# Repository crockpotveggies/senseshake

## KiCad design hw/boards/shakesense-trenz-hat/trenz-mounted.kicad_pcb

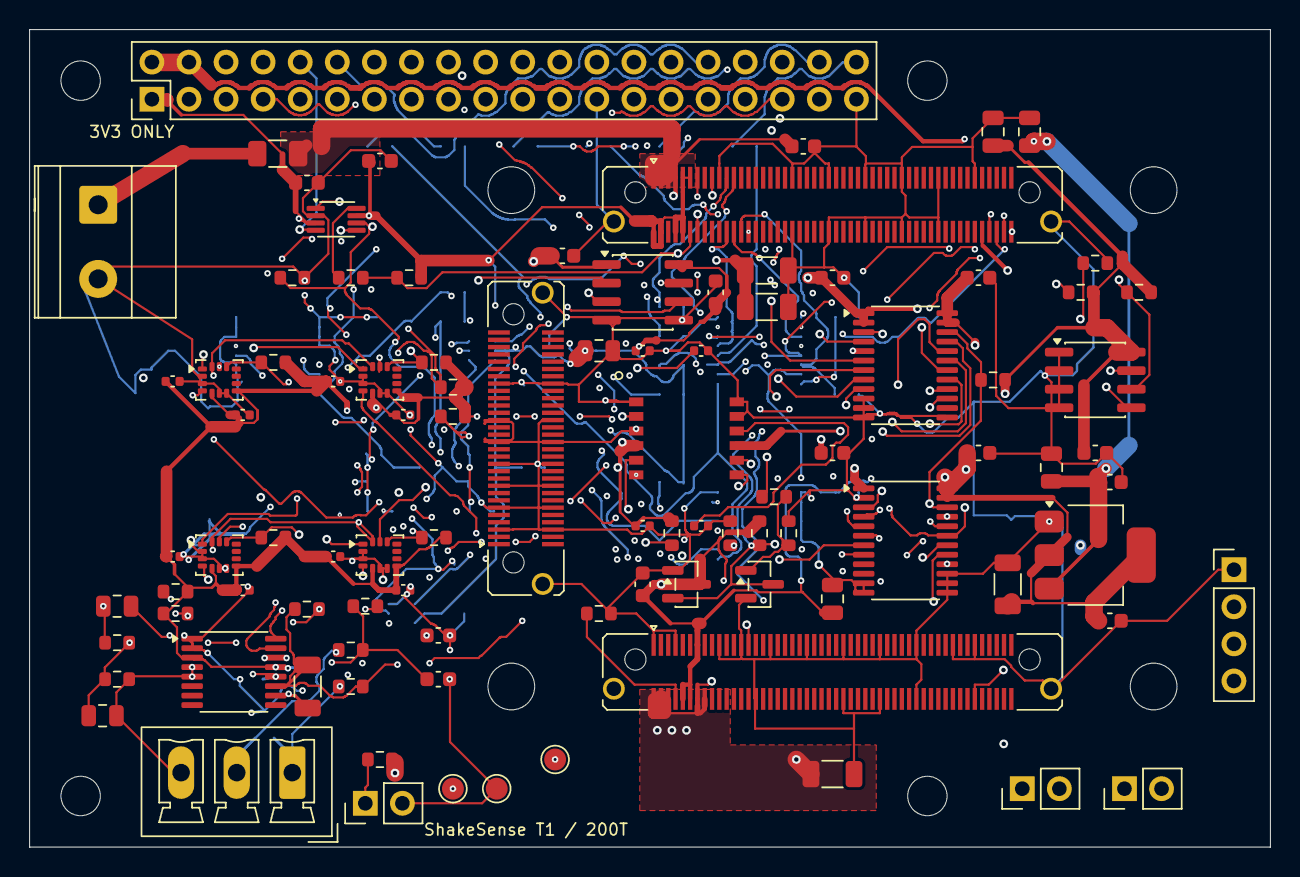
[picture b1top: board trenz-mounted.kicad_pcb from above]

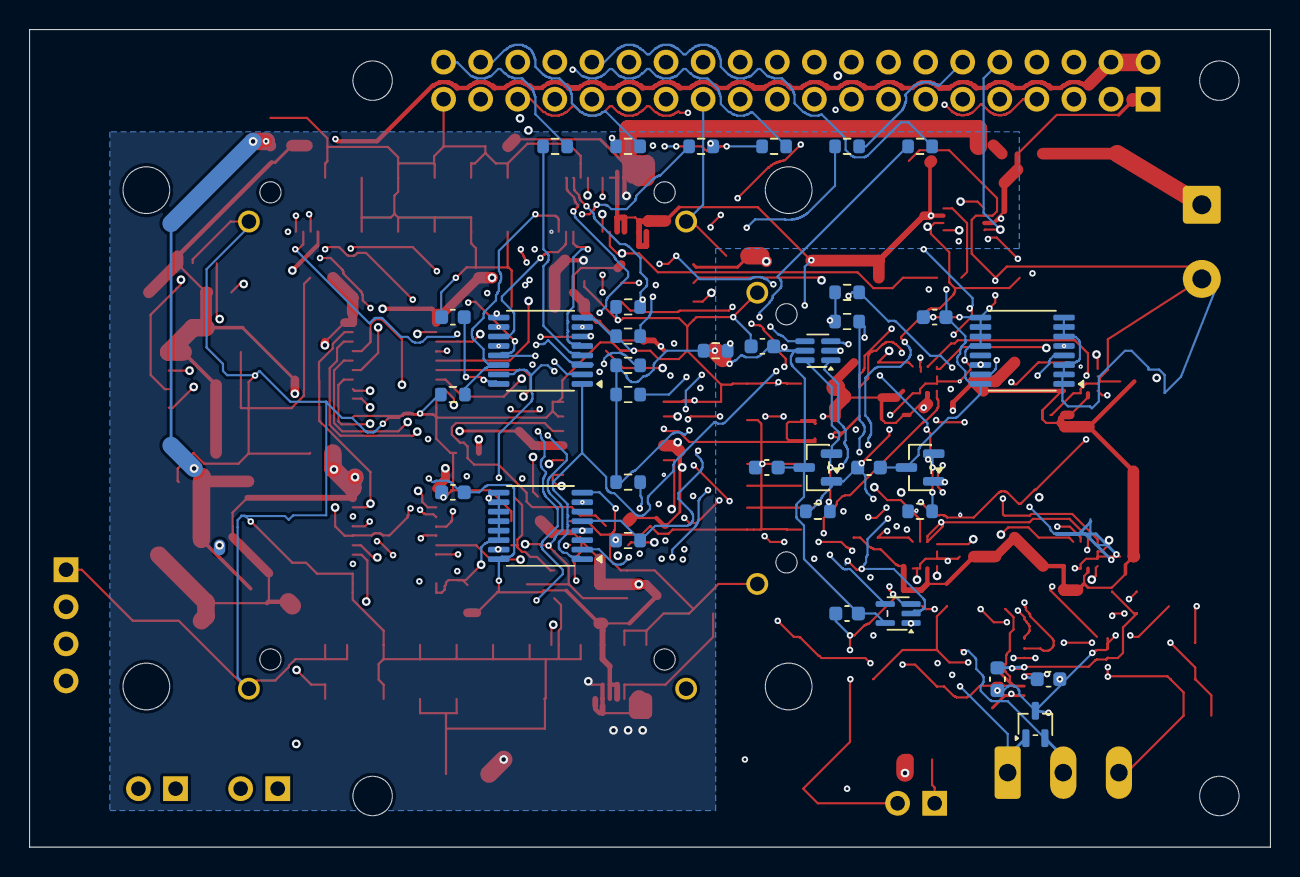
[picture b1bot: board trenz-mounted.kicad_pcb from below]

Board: 8 copper layers, 85.0 x 56.0 mm, 140 parts (35 on the bottom side), 90 nets.

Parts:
C1, C41, C43, C44, C45, C46, C47, C48, C49, C75, C76, C77, C83, C95, C96, C100, C101, C102, C103, C104, C105: 100n; Capacitor_SMD__C_0603_1608Metric
C2, C3, C40, C93, C94: 10u; Capacitor_SMD__C_0805_2012Metric
C12, C13, C14, C15, C16, C17, C18, C19, C20, C21, C22, C23: 100n; Capacitor_SMD__C_0402_1005Metric
C42, C80, C81, C82: 22u; Capacitor_SMD__C_1206_3216Metric
C84, C85: 4.7u; Capacitor_SMD__C_0805_2012Metric
C90: 100n C0G; Capacitor_SMD__C_1206_3216Metric
C91, C92: 1n C0G; Capacitor_SMD__C_0603_1608Metric
C106: Capacitor_SMD__C_0603_1608Metric
D90: TPD2E2U06; Package_TO_SOT_SMD__SOT-323_SC-70
F80: 0467005.NR; TZ_TZ_FUSE
H1, H2, H3, H4: M2.5 NPTH; MountingHole__MountingHole_2.7mm_M2.5
H80, H81, H82, H83: M3 / 8 mm spacer; TZ_TZ_HOLE
J1: Raspberry Pi 40-pin; Connector_PinHeader_2.54mm__PinHeader_2x20_P2.54mm_Vertical
J4: FPGA test UART/reset; Connector_PinHeader_2.54mm__PinHeader_1x04_P2.54mm_Vertical
J80, J81: LSHM-150-04.0-L-DV-A-S-K-TR; TZ_TZ100
J82: LSHM-130-04.0-L-DV-A-S-K-TR; TZ_TZ60
J83: 1715721; TZ_TZ_POWER
J90: GEO + / - / SHIELD; Connector_Phoenix_MC__PhoenixContact_MCV_1,5_3-G-3.81_1x03_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
JP1: EEPROM write enable; Connector_PinHeader_2.54mm__PinHeader_1x02_P2.54mm_Vertical
JP80, JP81: TSW-102-07-G-S; TZ_TZ_JP
MODEL_SPACERS: Visualization only
MODEL_TE0712: Visualization only
Q1: 2N7002; Package_TO_SOT_SMD__SOT-23
R1, R2: 3.9k; Resistor_SMD__R_0603_1608Metric
R3, R65, R90, R91: 1k; Resistor_SMD__R_0603_1608Metric
R11, R12, R13, R14, R20, R50, R63, R64, R80, R81, R94, R95, R97, R106, R107, R108, R109, R110, R111, R113, R115: 10k; Resistor_SMD__R_0603_1608Metric
R51, R62, R66, R112, R114, R116, R117: 100k; Resistor_SMD__R_0603_1608Metric
R52, R53: 4.7k; Resistor_SMD__R_0603_1608Metric
R61: 47; Resistor_SMD__R_0603_1608Metric
R92, R93: 1M; Resistor_SMD__R_0603_1608Metric
R96, R100, R101, R102, R103, R104, R105: 22; Resistor_SMD__R_0603_1608Metric
TP1: SENS_3V3; TestPoint__TestPoint_Pad_D1.5mm
TP2: GND; TestPoint__TestPoint_Pad_D1.5mm
TP4: SENSOR_OE_N; TestPoint__TestPoint_Pad_D1.5mm
U1: 24LC32A; Package_SO__SOIC-8_3.9x4.9mm_P1.27mm
U11, U12, U13, U14: LSM6DSOTR; Package_LGA__LGA-14_3x2.5mm_P0.5mm_LayoutBorder3x4y
U20: SCL3300-D01; ShakeSense__SCL3300_D01
U22: ADS122C04; Package_SO__TSSOP-16_4.4x5mm_P0.65mm
U40: TLV1117LV33DCYR; Package_TO_SOT_SMD__SOT-223-3_TabPin2
U41, U42: SN74LVC8T245PWR; Package_SO__TSSOP-24_4.4x7.8mm_P0.65mm
U43: ISO1640BDR; Package_SO__SOIC-8_3.9x4.9mm_P1.27mm
U51: TXU0202DCUR; Package_SO__VSSOP-8_2.3x2mm_P0.5mm
U52: TLV803EA30DBZR; Package_TO_SOT_SMD__SOT-23
U100, U101: TMUX1574PWR; Package_SO__TSSOP-16_4.4x5mm_P0.65mm
U102: TCA9534PWR; Package_SO__TSSOP-16_4.4x5mm_P0.65mm
U103: SN74LVC1G10DCKR; Package_TO_SOT_SMD__SOT-363_SC-70-6
U104, U105: TLV809EA30DBZR; Package_TO_SOT_SMD__SOT-23
U106: Package_TO_SOT_SMD__SOT-353_SC-70-5

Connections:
EEP_WP: JP1.1, R3.1, U1.7
EXT_3V3: F80.1, J83.1
FPGA_3V3: C76.1, C77.1, C84.1, C85.1, C100.1, C101.1, C103.1, C105.1, C106.1, J80.10, J80.12, J80.13, J81.2, J81.4, J81.8, J81.9, J81.10, J81.11, J81.92, R63.2, R64.2, R108.2, R111.2, R113.2, R115.2, U51.7, U52.3, U100.16, U101.16, U103.5, U105.3, U106.5
FPGA_CONFIG_RESET_N: J81.17, JP81.1
FPGA_EN1: J80.27, JP80.1
FPGA_IO_ENABLE: J1.22, R62.1, U51.6, U106.2
FPGA_JTAGEN: J80.90, R80.1
FPGA_LINK_CS_N: J81.23, R111.1, U101.2
FPGA_LINK_DQ0: J81.22, U100.5
FPGA_LINK_DQ1: J81.24, U100.11
FPGA_LINK_DQ2: J81.26, R116.1, U100.14
FPGA_LINK_DQ3: J81.28, R117.1, U101.5
FPGA_LINK_SCLK: J81.21, R112.1, U100.2
FPGA_NOSEQ: J80.8, R81.1
FPGA_RESET_GATE: Q1.1, R65.2, R66.1
FPGA_RESET_GPIO: J1.11, R65.1
FPGA_RESET_N: J4.4, J81.13, Q1.3, R64.1, U52.2
FPGA_UART_DRIVE: R61.1, U51.8
FPGA_UART_RX: J4.2, J81.12, R61.2, R63.1
FPGA_UART_TX: J4.3, J81.14, U51.1
FPGA_VIN: C80.1, C81.1, C82.1, C83.1, F80.2, J80.2, J80.4, J80.6, J80.14, J80.16, J81.1, J81.3, J81.5, J81.7
GEO_AIN_N: C90.2, C92.1, R91.2, R93.1, U22.10
GEO_AIN_P: C90.1, C91.1, R90.2, R92.1, U22.11
GEO_AVDD: C94.1, C95.1, R94.1, R96.2, U22.12
GEO_DRDY_N: R97.1, U22.14, U42.16
GEO_N: D90.2, J90.2, R91.1
GEO_P: D90.1, J90.1, R90.1
GEO_VCM: C93.1, R92.2, R93.2, R94.2, R95.1
GND: C1.2, C2.2, C3.2, C12.2, C13.2, C14.2, C15.2, C16.2, C17.2, C18.2, C19.2, C20.2, C21.2, C22.2, C23.2, C40.2, C41.2, C42.2, C43.2, C44.2, C45.2, C46.2, C47.2, C48.2, C49.2, C75.2, C76.2, C77.2, C80.2, C81.2, C82.2, C83.2, C84.2, C85.2, C91.2, C92.2, C93.2, C94.2, C95.2, C96.2, C100.2, C101.2, C102.2, C103.2, C104.2, C105.2, C106.2, D90.3, J1.6, J1.9, J1.14, J1.20, J1.25, J1.30, J1.34, J1.39, J4.1, J80.1, J80.7, J80.19, J80.25, J80.30, J80.33, J80.43, J80.53, J80.54, J80.63, J80.64, J80.73, J80.74, J80.83, J80.89, J80.101, J81.19, J81.39, J81.40, J81.49, J81.50, J81.59, J81.60, J81.69, J81.70, J81.79, J81.80, J81.89, J81.101, J82.5, J82.6, J82.11, J82.12, J82.17, J82.18, J82.23, J82.24, J82.29, J82.30, J82.35, J82.36, J82.45, J82.46, J82.61, J83.2, J90.3, JP1.2, JP80.2, JP81.2, Q1.2, R51.2, R62.2, R66.2, R80.2, R81.2, R95.2, R106.2, R107.2, R109.2, R110.2, R112.2, R114.2, R116.2, R117.2, TP2.1, U1.1, U1.2, U1.3, U1.4, U11.2, U11.3, U11.6, U11.7, U12.2, U12.3, U12.6, U12.7, U13.2, U13.3, U13.6, U13.7, U14.2, U14.3, U14.6, U14.7, U20.1, U20.3, U20.11, U20.12, U22.1, U22.2, U22.4, U22.5, U40.1, U41.10, U41.11, U41.12, U41.13, U42.2, U42.11, U42.12, U42.13, U42.14, U42.15, U43.4, U43.5, U51.2, U52.1, U100.8, U101.8, U101.9, U101.10, U101.11, U101.12, U101.13, U101.14, U102.1, U102.2, U102.3, U102.6, U102.7, U102.8, U102.9, U102.10, U102.11, U102.12, U103.2, U104.1, U105.1, U106.3
I2C_SCL: R53.1, U22.16, U43.6
I2C_SDA: R52.1, U22.15, U43.7
ID_SCL: J1.28, R2.1, U1.6
ID_SDA: J1.27, R1.1, U1.5
IMU1_CS: R11.1, U11.12, U41.19
IMU1_INT: U11.4, U42.20
IMU2_CS: R12.1, U12.12, U41.18
IMU2_INT: U12.4, U42.19
IMU3_CS: R13.1, U13.12, U41.17
IMU3_INT: U13.4, U42.18
IMU4_CS: R14.1, U14.12, U41.16
IMU4_INT: U14.4, U42.17
JTAG_TCK: J81.100, R114.1, U100.3
JTAG_TDI: J81.96, R115.1, U100.6
JTAG_TDO: J81.98, U100.10
JTAG_TMS: J81.94, R113.1, U100.13
LINK_ARMED_REQUEST: U103.1, U106.4
LINK_CS_N: R104.2, U101.4
LINK_DQ0: R101.2, U100.7
LINK_DQ1: R102.2, U100.9
LINK_DQ2: R103.2, U100.12
LINK_DQ3: R105.2, U101.7
LINK_FPGA_GOOD: R110.1, U103.6, U105.2
LINK_JTAG_SEL: R106.1, U100.1, U101.1, U102.4
LINK_OE_N: R108.1, U100.15, U101.15, U103.4
LINK_PI_GOOD: R109.1, U103.3, U104.2
LINK_REQUEST: R107.1, U102.5, U106.1
LINK_SCLK: R100.2, U100.4
PI_3V3: C1.1, C2.1, C44.1, C46.1, C48.1, C75.1, C102.1, C104.1, J1.1, J1.17, R1.2, R2.2, R3.2, R50.2, U1.8, U41.1, U41.2, U42.1, U43.1, U51.3, U102.16, U104.3
PI_5V: C3.1, C40.1, C41.1, J1.2, J1.4, U40.3
PI_GEO_DRDY_N: J1.7, U42.8
PI_I2C_SCL: J1.5, U43.3, U102.14
PI_I2C_SDA: J1.3, U43.2, U102.15
PI_IMU1_CS: J1.24, U41.5
PI_IMU1_INT: J1.13, U42.4
PI_IMU2_CS: J1.26, U41.6
PI_IMU2_INT: J1.15, U42.5
PI_IMU3_CS: J1.29, U41.7
PI_IMU3_INT: J1.16, U42.6
PI_IMU4_CS: J1.31, U41.8
PI_IMU4_INT: J1.18, U42.7
PI_LINK_CS_N: J1.12, R104.1
PI_LINK_DQ0: J1.38, R101.1
PI_LINK_DQ1: J1.35, R102.1
PI_LINK_DQ2: J1.36, R103.1
PI_LINK_DQ3: J1.32, R105.1
PI_LINK_SCLK: J1.40, R100.1
PI_SPI_MISO: J1.21, U42.3
PI_SPI_MOSI: J1.19, U41.3
PI_SPI_SCLK: J1.23, U41.4
PI_TILT_CS: J1.33, U41.9
PI_UART_RX: J1.10, U51.4
PI_UART_TX: J1.8, U51.5
SENSOR_OE_N: J1.37, R50.1, TP4.1, U41.22, U42.22
SENS_3V3: C12.1, C13.1, C14.1, C15.1, C16.1, C17.1, C18.1, C19.1, C20.1, C22.1, C42.1, C43.1, C45.1, C47.1, C49.1, C96.1, R11.2, R12.2, R13.2, R14.2, R20.2, R52.2, R53.2, R96.1, R97.2, TP1.1, U11.5, U11.8, U12.5, U12.8, U13.5, U13.8, U14.5, U14.8, U20.4, U20.9, U22.3, U22.13, U40.2, U41.23, U41.24, U42.23, U42.24, U43.8
SPI_MISO: R51.1, U11.1, U12.1, U13.1, U14.1, U20.6, U42.21
SPI_MOSI: U11.14, U12.14, U13.14, U14.14, U20.7, U41.21
SPI_SCLK: U11.13, U12.13, U13.13, U14.13, U20.8, U41.20
TILT_AEXT: C21.1, U20.2
TILT_CS: R20.1, U20.5, U41.15
TILT_DEXT: C23.1, U20.10

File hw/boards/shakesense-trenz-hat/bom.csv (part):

Reference,Value,MPN,Footprint,DNP,Note
J1,Raspberry Pi 40-pin,Samtec ESQ-120-23-G-D,Connector_PinHeader_2.54mm__PinHeader_2x20_P2.54mm_Vertical,False,"Header land pattern matches bottom mounted socket top-view numbering; tall stack, check Pi 4/5 cooler clearance."
U1,24LC32A,24LC32A-I/SN,Package_SO__SOIC-8_3.9x4.9mm_P1.27mm,False,
R1,3.9k,RC0603FR-073K9L,Resistor_SMD__R_0603_1608Metric,False,
R2,3.9k,RC0603FR-073K9L,Resistor_SMD__R_0603_1608Metric,False,
R3,1k,RC0603FR-071KL,Resistor_SMD__R_0603_1608Metric,False,
JP1,EEPROM write enable,EEPROM write enable,Connector_PinHeader_2.54mm__PinHeader_1x02_P2.54mm_Vertical,False,Fit shunt only while programming ID EEPROM.
C1,100n,GRM188R71H104KA93D,Capacitor_SMD__C_0603_1608Metric,False,
C2,10u,GRM21BR61A106KE19L,Capacitor_SMD__C_0805_2012Metric,False,
C3,10u,GRM21BR61A106KE19L,Capacitor_SMD__C_0805_2012Metric,False,
U11,LSM6DSOTR,LSM6DSOTR,Package_LGA__LGA-14_3x2.5mm_P0.5mm_LayoutBorder3x4y,False,
C12,100n,GRM155R71C104KA88D,Capacitor_SMD__C_0402_1005Metric,False,
C13,100n,GRM155R71C104KA88D,Capacitor_SMD__C_0402_1005Metric,False,
R11,10k,RC0603FR-0710KL,Resistor_SMD__R_0603_1608Metric,False,
U12,LSM6DSOTR,LSM6DSOTR,Package_LGA__LGA-14_3x2.5mm_P0.5mm_LayoutBorder3x4y,False,
C14,100n,GRM155R71C104KA88D,Capacitor_SMD__C_0402_1005Metric,False,
C15,100n,GRM155R71C104KA88D,Capacitor_SMD__C_0402_1005Metric,False,
R12,10k,RC0603FR-0710KL,Resistor_SMD__R_0603_1608Metric,False,
U13,LSM6DSOTR,LSM6DSOTR,Package_LGA__LGA-14_3x2.5mm_P0.5mm_LayoutBorder3x4y,False,
C16,100n,GRM155R71C104KA88D,Capacitor_SMD__C_0402_1005Metric,False,
C17,100n,GRM155R71C104KA88D,Capacitor_SMD__C_0402_1005Metric,False,
R13,10k,RC0603FR-0710KL,Resistor_SMD__R_0603_1608Metric,False,
U14,LSM6DSOTR,LSM6DSOTR,Package_LGA__LGA-14_3x2.5mm_P0.5mm_LayoutBorder3x4y,False,
C18,100n,GRM155R71C104KA88D,Capacitor_SMD__C_0402_1005Metric,False,
C19,100n,GRM155R71C104KA88D,Capacitor_SMD__C_0402_1005Metric,False,
R14,10k,RC0603FR-0710KL,Resistor_SMD__R_0603_1608Metric,False,
U20,SCL3300-D01,SCL3300-D01-10,ShakeSense__SCL3300_D01,False,
C20,100n,GRM155R71C104KA88D,Capacitor_SMD__C_0402_1005Metric,False,
C21,100n,GRM155R71C104KA88D,Capacitor_SMD__C_0402_1005Metric,False,
C22,100n,GRM155R71C104KA88D,Capacitor_SMD__C_0402_1005Metric,False,
C23,100n,GRM155R71C104KA88D,Capacitor_SMD__C_0402_1005Metric,False,
R20,10k,RC0603FR-0710KL,Resistor_SMD__R_0603_1608Metric,False,
J4,FPGA test UART/reset,Coldfoot UART service ONLY,Connector_PinHeader_2.54mm__PinHeader_1x04_P2.54mm_Vertical,False,Test points for assembled module UART and active-low reset; do not connect a second driving host.
H1,M2.5 NPTH,M2.5 NPTH,MountingHole__MountingHole_2.7mm_M2.5,False,Nonmagnetic standoffs.
H2,M2.5 NPTH,M2.5 NPTH,MountingHole__MountingHole_2.7mm_M2.5,False,Nonmagnetic standoffs.
H3,M2.5 NPTH,M2.5 NPTH,MountingHole__MountingHole_2.7mm_M2.5,False,Nonmagnetic standoffs.
H4,M2.5 NPTH,M2.5 NPTH,MountingHole__MountingHole_2.7mm_M2.5,False,Nonmagnetic standoffs.
U40,TLV1117LV33DCYR,TLV1117LV33DCYR,Package_TO_SOT_SMD__SOT-223-3_TabPin2,False,
C40,10u,GRM21BR61A106KE19L,Capacitor_SMD__C_0805_2012Metric,False,
C41,100n,GRM188R71H104KA93D,Capacitor_SMD__C_0603_1608Metric,False,
C42,22u,GRM31CR61A226KE19L,Capacitor_SMD__C_1206_3216Metric,False,
C43,100n,GRM188R71H104KA93D,Capacitor_SMD__C_0603_1608Metric,False,
U41,SN74LVC8T245PWR,SN74LVC8T245PWR,Package_SO__TSSOP-24_4.4x7.8mm_P0.65mm,False,
U42,SN74LVC8T245PWR,SN74LVC8T245PWR,Package_SO__TSSOP-24_4.4x7.8mm_P0.65mm,False,
C44,100n,GRM188R71H104KA93D,Capacitor_SMD__C_0603_1608Metric,False,
C45,100n,GRM188R71H104KA93D,Capacitor_SMD__C_0603_1608Metric,False,
C46,100n,GRM188R71H104KA93D,Capacitor_SMD__C_0603_1608Metric,False,
C47,100n,GRM188R71H104KA93D,Capacitor_SMD__C_0603_1608Metric,False,
R50,10k,RC0603FR-0710KL,Resistor_SMD__R_0603_1608Metric,False,
R51,100k,RC0603FR-07100KL,Resistor_SMD__R_0603_1608Metric,False,
U43,ISO1640BDR,ISO1640BDR,Package_SO__SOIC-8_3.9x4.9mm_P1.27mm,False,Power-domain isolation only: grounds are joined. Side-1 VOL max 0.71V requires host VIL >=0.8V; verify Pi revision.
C48,100n,GRM188R71H104KA93D,Capacitor_SMD__C_0603_1608Metric,False,
C49,100n,GRM188R71H104KA93D,Capacitor_SMD__C_0603_1608Metric,False,
R52,4.7k,RC0603FR-074K7L,Resistor_SMD__R_0603_1608Metric,False,
R53,4.7k,RC0603FR-074K7L,Resistor_SMD__R_0603_1608Metric,False,
TP1,SENS_3V3,SENS_3V3,TestPoint__TestPoint_Pad_D1.5mm,False,
TP2,GND,GND,TestPoint__TestPoint_Pad_D1.5mm,False,
TP4,SENSOR_OE_N,SENSOR_OE_N,TestPoint__TestPoint_Pad_D1.5mm,False,
U51,TXU0202DCUR,TXU0202DCUR,Package_SO__VSSOP-8_2.3x2mm_P0.5mm,False,
C75,100n,GRM188R71H104KA93D,Capacitor_SMD__C_0603_1608Metric,False,
C76,100n,GRM188R71H104KA93D,Capacitor_SMD__C_0603_1608Metric,False,
R61,47,RC0603FR-0747RL,Resistor_SMD__R_0603_1608Metric,False,
R62,100k,RC0603FR-07100KL,Resistor_SMD__R_0603_1608Metric,False,
R63,10k,RC0603FR-0710KL,Resistor_SMD__R_0603_1608Metric,False,
U52,TLV803EA30DBZR,TLV803EA30DBZR,Package_TO_SOT_SMD__SOT-23,False,"3.0V falling threshold, 200ms nominal release delay; open-drain output."
C77,100n,GRM188R71H104KA93D,Capacitor_SMD__C_0603_1608Metric,False,
R64,10k,RC0603FR-0710KL,Resistor_SMD__R_0603_1608Metric,False,
Q1,2N7002,2N7002,Package_TO_SOT_SMD__SOT-23,False,Pi GPIO17 HIGH asserts chip reset; does not drive a live voltage into unpowered chip.
R65,1k,RC0603FR-071KL,Resistor_SMD__R_0603_1608Metric,False,
R66,100k,RC0603FR-07100KL,Resistor_SMD__R_0603_1608Metric,False,
J80,LSHM-150-04.0-L-DV-A-S-K-TR,LSHM-150-04.0-L-DV-A-S-K-TR,TZ_TZ100,False,Mates JM1; opposite parity; 8 mm board surface gap
J81,LSHM-150-04.0-L-DV-A-S-K-TR,LSHM-150-04.0-L-DV-A-S-K-TR,TZ_TZ100,False,Mates JM2; opposite parity; 8 mm board surface gap
J82,LSHM-130-04.0-L-DV-A-S-K-TR,LSHM-130-04.0-L-DV-A-S-K-TR,TZ_TZ60,False,Mates JM3; opposite parity; 8 mm board surface gap
J83,1715721,1715721,TZ_TZ_POWER,False,REGULATED 3.3 V ONLY; external current-limited supply; 3 A initial operating budget Shifted left to keep power-terminal tails out of the J86 ribbon corridor.
F80,0467005.NR,0467005.NR,TZ_TZ_FUSE,False,5 A fast fuse; not reverse-polarity or overvoltage protection
JP80,TSW-102-07-G-S,TSW-102-07-G-S,TZ_TZ_JP,False,Fit shunt to DISABLE module; open enables on-board sequence
JP81,TSW-102-07-G-S,TSW-102-07-G-S,TZ_TZ_JP,False,Fit shunt to request module configuration reset
R80,10k,RC0603FR-0710KL,Resistor_SMD__R_0603_1608Metric,False,FPGA JTAG selection / spare CPLD control idle pull-down
R81,10k,RC0603FR-0710KL,Resistor_SMD__R_0603_1608Metric,False,FPGA JTAG selection / spare CPLD control idle pull-down
C80,22u,GRM31CR61A226KE19L,Capacitor_SMD__C_1206_3216Metric,False,Carrier local decoupling; module contains core decoupling
C81,22u,GRM31CR61A226KE19L,Capacitor_SMD__C_1206_3216Metric,False,Carrier local decoupling; module contains core decoupling
C82,22u,GRM31CR61A226KE19L,Capacitor_SMD__C_1206_3216Metric,False,Carrier local decoupling; module contains core decoupling
C83,100n,GRM188R71H104KA93D,Capacitor_SMD__C_0603_1608Metric,False,Carrier local decoupling; module contains core decoupling
C84,4.7u,GRM21BR71A475KA73L,Capacitor_SMD__C_0805_2012Metric,False,Carrier local decoupling; module contains core decoupling
C85,4.7u,GRM21BR71A475KA73L,Capacitor_SMD__C_0805_2012Metric,False,Carrier local decoupling; module contains core decoupling
H80,M3 / 8 mm spacer,M3 / 8 mm spacer,TZ_TZ_HOLE,False,
H81,M3 / 8 mm spacer,M3 / 8 mm spacer,TZ_TZ_HOLE,False,
H82,M3 / 8 mm spacer,M3 / 8 mm spacer,TZ_TZ_HOLE,False,
H83,M3 / 8 mm spacer,M3 / 8 mm spacer,TZ_TZ_HOLE,False,
U22,ADS122C04,ADS122C04IPWR,Package_SO__TSSOP-16_4.4x5mm_P0.65mm,False,"I2C 0x40; internal 2.048V reference, gain 64, normal 330 SPS; unused analog/reference inputs open per TI."
J90,GEO + / - / SHIELD,1803439,"Connector_Phoenix_MC__PhoenixContact_MCV_1,5_3-G-3.81_1x03_P3.81mm_Vertical",False,"External passive sensor: 1 positive, 2 negative, 3 cable shield. Mate MC 1,5/3-ST-3,81. Never connect power."
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
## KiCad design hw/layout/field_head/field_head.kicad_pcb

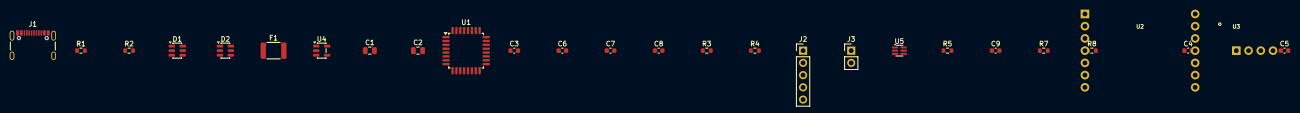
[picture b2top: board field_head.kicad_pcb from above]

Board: 2 copper layers, 27 parts (0 on the bottom side), 17 nets, no tracks yet.

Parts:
C1, C2: Capacitor_SMD__C_0805_2012Metric
C3, C4, C5, C6, C7, C8, C9: Capacitor_SMD__C_0603_1608Metric
D1, D2: Package_TO_SOT_SMD__SOT-23-6
F1: Fuse__Fuse_1812_4532Metric
J1: Connector_USB__USB_C_Receptacle_GCT_USB4105-xx-A_16P_TopMnt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
J2: Connector_PinHeader_2.54mm__PinHeader_1x05_P2.54mm_Vertical
J3: Connector_PinHeader_2.54mm__PinHeader_1x02_P2.54mm_Vertical
R1, R2, R3, R4, R5, R7, R8: Resistor_SMD__R_0603_1608Metric
U1: Package_QFP__LQFP-32_7x7mm_P0.8mm
U2: Groundlark__PNI_14190_Module
U3: Groundlark__DLVR_E1BS
U4: Package_TO_SOT_SMD__SOT-23-5
U5: Package_TO_SOT_SMD__SOT-363_SC-70-6

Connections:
BOOT0: J3.2, R4.1, U1.31
GND: C1.2, C2.2, C3.2, C4.2, C5.2, C6.2, C7.2, C8.2, C9.2, D1.2, D2.2, J1.A1, J1.A12, J1.B1, J1.B12, J1.S1, J2.3, R1.2, R2.2, R4.2, R5.2, U1.16, U1.32, U2.2, U2.4, U2.7, U2.14, U3.1, U4.2, U5.2
MAG_DRDY: U1.14, U2.5
NRST: C8.1, J2.5, R3.2, U1.4
SCL: R8.1, U1.29, U2.1, U3.4
SDA: R7.1, U1.30, U2.3, U3.3
SENSOR_EN: R5.1, U1.6, U5.3
SWCLK: J2.4, U1.24
SWDIO: J2.2, U1.23
USB_5V: C1.1, F1.2, U4.1, U4.3
USB_CC1: D2.1, D2.6, J1.A5, R1.1
USB_CC2: D2.3, D2.4, J1.B5, R2.1
USB_DM: D1.3, D1.4, J1.A7, J1.B7, U1.21
USB_DP: D1.1, D1.6, J1.A6, J1.B6, U1.22
USB_VBUS: D1.5, D2.5, F1.1, J1.A4, J1.A9, J1.B4, J1.B9
V3: C2.1, C3.1, C6.1, C7.1, C9.1, J2.1, J3.1, R3.1, U1.1, U1.5, U1.17, U4.5, U5.1
V3_SENSOR: C4.1, C5.1, R7.2, R8.2, U2.10, U2.12, U2.13, U3.2, U5.5, U5.6

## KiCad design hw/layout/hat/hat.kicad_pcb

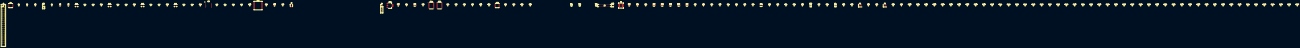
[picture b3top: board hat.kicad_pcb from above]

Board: 2 copper layers, 143 parts (0 on the bottom side), 106 nets, no tracks yet.

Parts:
C1, C24, C26, C41, C43, C44, C45, C46, C47, C48, C49, C62, C67, C68, C69, C70, C71, C72, C73, C74, C75, C76, C77, C78, C79: Capacitor_SMD__C_0603_1608Metric
C2, C3, C25, C40, C60, C61: Capacitor_SMD__C_0805_2012Metric
C12, C13, C14, C15, C16, C17, C18, C19, C20, C21, C22, C23: Capacitor_SMD__C_0402_1005Metric
C42, C63, C64, C65, C66: Capacitor_SMD__C_1206_3216Metric
J1: Connector_PinHeader_2.54mm__PinHeader_2x20_P2.54mm_Vertical
J2: Connector_Coaxial__U.FL_Hirose_U.FL-R-SMT-1_Vertical
J4: Connector_PinHeader_2.54mm__PinHeader_1x04_P2.54mm_Vertical
J5: Coldfoot_Run1_70DS
JP1: Connector_PinHeader_2.54mm__PinHeader_1x02_P2.54mm_Vertical
L1: Inductor_SMD__L_Bourns_SRN6045TA
Q1: Package_TO_SOT_SMD__SOT-23
R1, R2, R3, R11, R12, R13, R14, R20, R50, R51, R52, R53, R61, R62, R63, R64, R65, R66, R67, R68, R100, R101, R102, R103, R104, R105, R106, R107, R108, R109, R110, R111, R112, R113, R114, R115, R116, R117, R118, R119, R120, R121, R122, R123, R124, R125, R126, R127, R128, R129, R130, R131, R132, R133, R134, R135, R136, R137, R138, R139, R140, R141, R142, R143, R144, R145, R146, R147: Resistor_SMD__R_0603_1608Metric
R60: Resistor_SMD__R_1206_3216Metric
TP1, TP2, TP4: TestPoint__TestPoint_Pad_D1.5mm
U1, U43: Package_SO__SOIC-8_3.9x4.9mm_P1.27mm
U11, U12, U13, U14: Package_LGA__LGA-14_3x2.5mm_P0.5mm_LayoutBorder3x4y
U20: Groundlark__SCL3300_D01
U21: RF_GPS__ublox_MAX
U40: Package_TO_SOT_SMD__SOT-223-3_TabPin2
U41, U42: Package_SO__TSSOP-24_4.4x7.8mm_P0.65mm
U50: Package_TO_SOT_SMD__TSOT-23-6
U51: Package_SO__VSSOP-8_2.3x2mm_P0.5mm
U52: Package_TO_SOT_SMD__SOT-23
Y1, Y2: Crystal__Crystal_SMD_3225-4Pin_3.2x2.5mm

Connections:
CF_3V3: C66.1, C67.1, C68.1, C69.1, C70.1, C71.1, C72.1, C73.1, C74.1, C76.1, C77.1, C78.1, C79.1, J5.9, J5.11, J5.19, J5.24, J5.44, J5.46, J5.54, J5.62, R60.2, R63.2, R64.2, R111.2, R122.2, R135.2, R141.2, U51.7, U52.3, Y1.1, Y1.4, Y2.1, Y2.4
CF_BIDIR_2: J5.4, R110.1
CF_BIDIR_3: J5.3, R111.1
CF_BIDIR_4: J5.2, R112.1
CF_BIDIR_5: J5.1, R113.1
CF_BIDIR_6: J5.70, R114.1
CF_BIDIR_7: J5.69, R115.1
CF_BIDIR_8: J5.68, R116.1
CF_BIDIR_9: J5.67, R117.1
CF_BIDIR_10: J5.66, R118.1
CF_BIDIR_11: J5.65, R119.1
CF_BIDIR_12: J5.64, R120.1
CF_BIDIR_13: J5.63, R121.1
CF_BIDIR_14: J5.60, R122.1
CF_BIDIR_15: J5.59, R123.1
CF_BIDIR_16: J5.58, R124.1
CF_BIDIR_17: J5.57, R125.1
CF_BIDIR_18: J5.56, R126.1
CF_BIDIR_19: J5.55, R127.1
CF_BIDIR_20: J5.52, R128.1
CF_BIDIR_21: J5.51, R129.1
CF_BIDIR_22: J5.50, R130.1
CF_BIDIR_23: J5.49, R131.1
CF_BIDIR_24: J5.48, R132.1
CF_BIDIR_25: J5.47, R133.1
CF_BIDIR_26: J5.43, R134.1
CF_BIDIR_27: J5.42, R135.1
CF_BIDIR_28: J5.41, R136.1
CF_BIDIR_29: J5.40, R137.1
CF_BIDIR_30: J5.39, R138.1
CF_BIDIR_31: J5.38, R139.1
CF_BIDIR_32: J5.37, R140.1
CF_BIDIR_33: J5.36, R141.1
CF_BIDIR_34: J5.35, R142.1
CF_BIDIR_35: J5.34, R143.1
CF_BIDIR_36: J5.33, R144.1
CF_BIDIR_37: J5.32, R145.1
CF_BIDIR_38: J5.31, R146.1
CF_BIDIR_39: J5.30, R147.1
CF_BST: C62.1, U50.6
CF_IN_1: J5.26, R100.1
CF_IN_2: J5.23, R101.1
CF_IN_4: J5.21, R102.1
CF_IN_5: J5.20, R103.1
CF_IN_6: J5.17, R104.1
CF_IN_7: J5.16, R105.1
CF_IN_8: J5.15, R106.1
CF_IN_9: J5.14, R107.1
CF_IN_10: J5.13, R108.1
CF_IN_11: J5.12, R109.1
CF_IO_ENABLE: J1.22, R62.1, U51.6
CF_MESH_CLK: J5.8, R67.2
CF_MESH_CLK_RAW: R67.1, Y1.3
CF_REG_3V3: C63.1, C64.1, C65.1, L1.2, R60.1, U50.1
CF_RESET_GATE: Q1.1, R65.2, R66.1
CF_RESET_GPIO: J1.11, R65.1
CF_RESET_N: J4.4, J5.7, Q1.3, R64.1, U52.2
CF_SW: C62.2, L1.1, U50.5
CF_TILE_CLK: J5.22, R68.2
CF_TILE_CLK_RAW: R68.1, Y2.3
CF_UART_DRIVE: R61.1, U51.8
CF_UART_RX: J4.2, J5.27, R61.2, R63.1
CF_UART_TX: J4.3, J5.6, U51.1
EEP_WP: JP1.1, R3.1, U1.7
GND: C1.2, C2.2, C3.2, C12.2, C13.2, C14.2, C15.2, C16.2, C17.2, C18.2, C19.2, C20.2, C21.2, C22.2, C23.2, C24.2, C25.2, C26.2, C40.2, C41.2, C42.2, C43.2, C44.2, C45.2, C46.2, C47.2, C48.2, C49.2, C60.2, C61.2, C63.2, C64.2, C65.2, C66.2, C67.2, C68.2, C69.2, C70.2, C71.2, C72.2, C73.2, C74.2, C75.2, C76.2, C77.2, C78.2, C79.2, J1.6, J1.9, J1.14, J1.20, J1.25, J1.30, J1.34, J1.39, J2.2, J4.1, J5.10, J5.18, J5.25, J5.45, J5.53, J5.61, JP1.2, Q1.2, R51.2, R62.2, R66.2, R100.2, R101.2, R102.2, R103.2, R104.2, R105.2, R106.2, R107.2, R108.2, R109.2, R110.2, R112.2, R113.2, R114.2, R115.2, R116.2, R117.2, R118.2, R119.2, R120.2, R121.2, R123.2, R124.2, R125.2, R126.2, R127.2, R128.2, R129.2, R130.2, R131.2, R132.2, R133.2, R134.2, R136.2, R137.2, R138.2, R139.2, R140.2, R142.2, R143.2, R144.2, R145.2, R146.2, R147.2, TP2.1, U1.1, U1.2, U1.3, U1.4, U11.2, U11.3, U11.6, U11.7, U12.2, U12.3, U12.6, U12.7, U13.2, U13.3, U13.6, U13.7, U14.2, U14.3, U14.6, U14.7, U20.1, U20.3, U20.11, U20.12, U21.1, U21.5, U21.10, U21.12, U40.1, U41.10, U41.11, U41.12, U41.13, U42.2, U42.11, U42.12, U42.13, U42.14, U42.15, U43.4, U43.5, U50.4, U51.2, U52.1, Y1.2, Y2.2
GNSS_PPS: U21.4, U42.16
GNSS_RF: J2.1, U21.11
I2C_SCL: R53.1, U21.17, U43.6
I2C_SDA: R52.1, U21.16, U43.7
ID_SCL: J1.28, R2.1, U1.6
ID_SDA: J1.27, R1.1, U1.5
IMU1_CS: R11.1, U11.12, U41.19
IMU1_INT: U11.4, U42.20
IMU2_CS: R12.1, U12.12, U41.18
IMU2_INT: U12.4, U42.19
IMU3_CS: R13.1, U13.12, U41.17
IMU3_INT: U13.4, U42.18
IMU4_CS: R14.1, U14.12, U41.16
IMU4_INT: U14.4, U42.17
PI_3V3: C1.1, C2.1, C44.1, C46.1, C48.1, C75.1, J1.1, J1.17, R1.2, R2.2, R3.2, R50.2, U1.8, U41.1, U41.2, U42.1, U43.1, U51.3
PI_5V: C3.1, C40.1, C41.1, C60.1, C61.1, J1.2, J1.4, U40.3, U50.2, U50.3
PI_GNSS_PPS: J1.7, U42.8
PI_I2C_SCL: J1.5, U43.3
PI_I2C_SDA: J1.3, U43.2
PI_IMU1_CS: J1.24, U41.5
PI_IMU1_INT: J1.13, U42.4
PI_IMU2_CS: J1.26, U41.6
PI_IMU2_INT: J1.15, U42.5
PI_IMU3_CS: J1.29, U41.7
PI_IMU3_INT: J1.16, U42.6
PI_IMU4_CS: J1.31, U41.8
PI_IMU4_INT: J1.18, U42.7
PI_SPI_MISO: J1.21, U42.3
PI_SPI_MOSI: J1.19, U41.3
PI_SPI_SCLK: J1.23, U41.4
PI_TILT_CS: J1.33, U41.9
PI_UART_RX: J1.10, U51.4
PI_UART_TX: J1.8, U51.5
SENSOR_OE_N: J1.37, R50.1, TP4.1, U41.22, U42.22
SENS_3V3: C12.1, C13.1, C14.1, C15.1, C16.1, C17.1, C18.1, C19.1, C20.1, C22.1, C24.1, C25.1, C26.1, C42.1, C43.1, C45.1, C47.1, C49.1, R11.2, R12.2, R13.2, R14.2, R20.2, R52.2, R53.2, TP1.1, U11.5, U11.8, U12.5, U12.8, U13.5, U13.8, U14.5, U14.8, U20.4, U20.9, U21.7, U21.8, U40.2, U41.23, U41.24, U42.23, U42.24, U43.8
SPI_MISO: R51.1, U11.1, U12.1, U13.1, U14.1, U20.6, U42.21
SPI_MOSI: U11.14, U12.14, U13.14, U14.14, U20.7, U41.21
SPI_SCLK: U11.13, U12.13, U13.13, U14.13, U20.8, U41.20
TILT_AEXT: C21.1, U20.2
TILT_CS: R20.1, U20.5, U41.15
TILT_DEXT: C23.1, U20.10
